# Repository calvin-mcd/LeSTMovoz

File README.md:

# LeSTMovoz
 
The LeSTMovoz is drop-in DIY replacement pcb for the [Lesovoz](https://trashman.wiki/community/pcbs/lesovoz) pcb by squash for [minivan](https://trashman.wiki/) style cases.
The replacement pcb adds a second 2u bottom row option by omitting one tray mount hole. [Existing plates](https://www.minivanplate.xyz/) should work but said 2u option is not accounted for in original plates.  

It uses mostly THT components to be added by hand, but production files exist to handle the few SMD components (STM32 mcu, logic shifter for rgb, usb port) with factory assembly.

Vial Firmware was created by JLW and can be found here: https://github.com/josh-l-wang/vial-qmk/tree/main-vial/keyboards/jlw/lestmovoz

## Layout

[Link](http://www.keyboard-layout-editor.com/#/gists/4bbcc5860d075f44de381a1146810c87)

## Todo

- [x] order & test pcb Rev 2
- [x] create firmware

## Disclaimer

This PCB has been fully tested and is confirmed to work. However, no-one involved in this project is responsible for any usage issues that may arise. Order at your own risk. Feel free to edit, modify and otherwise utilise these files.

## License

This project is released under the GPL v3 License. Please refer to the LICENCE file.

## Credits

Big thanks to JLW for supporting and making this project possible and to Kenny for getting it out there to people.

And as always big thanks to the 40s community!

Any questions, contact calvin0563 on Discord.

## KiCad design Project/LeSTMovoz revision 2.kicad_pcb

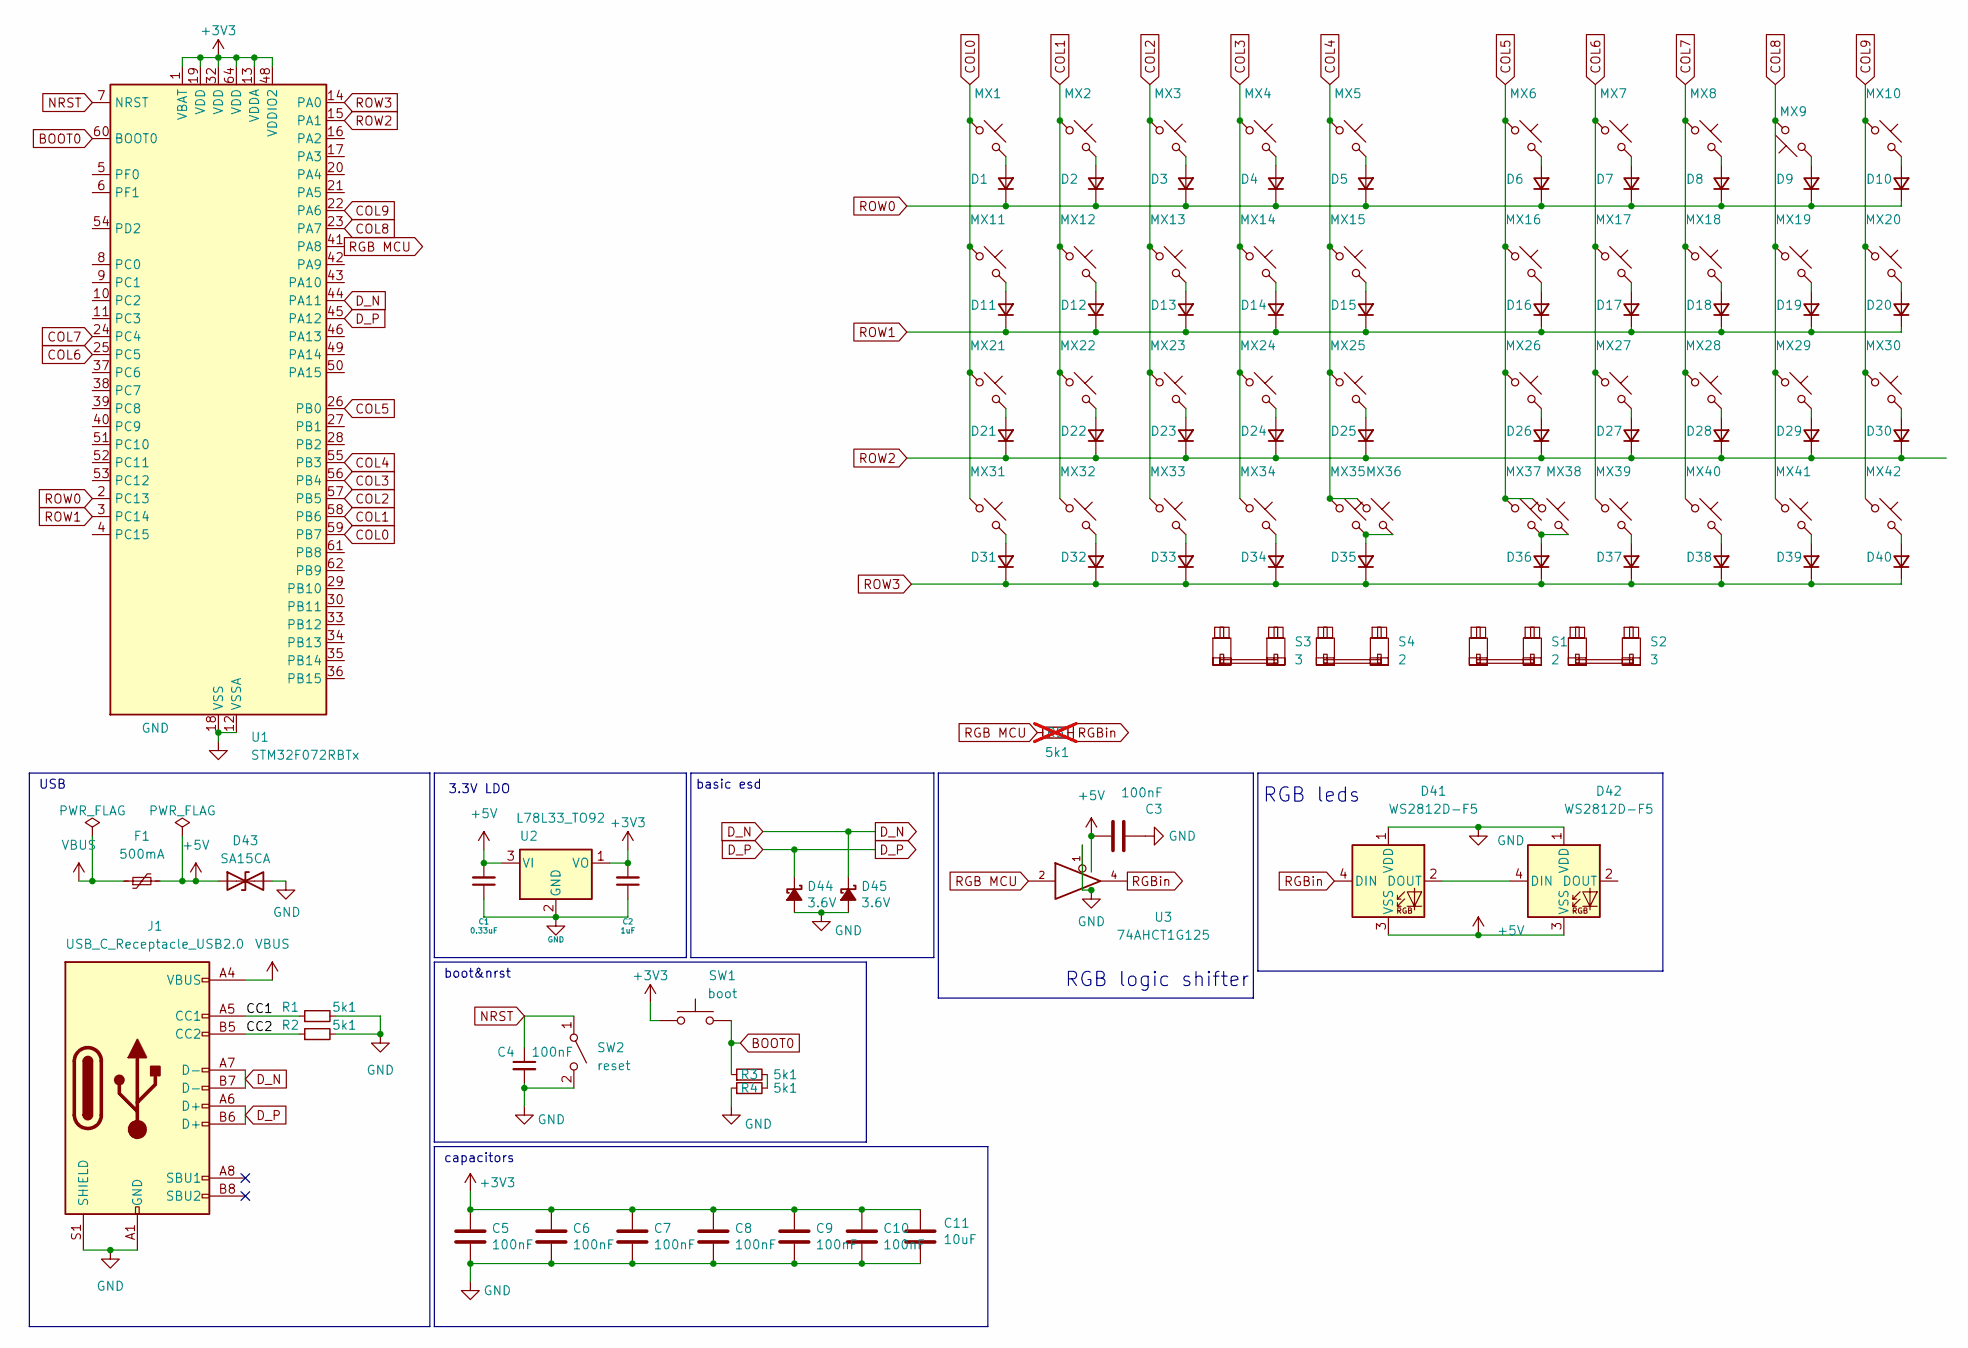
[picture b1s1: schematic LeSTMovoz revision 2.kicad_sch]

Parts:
C1: 0.33uF; C_Disc_D4.3mm_W1.9mm_P5.00mm
C2: 1uF; C_Disc_D4.3mm_W1.9mm_P5.00mm
C3, C4, C5, C6, C7, C8, C9, C10: 100nF; C_Disc_D4.3mm_W1.9mm_P5.00mm
C11: 10uF; C_Disc_D4.3mm_W1.9mm_P5.00mm
D1, D2, D3, D4, D5, D6, D7, D8, D9, D10, D11, D12, D13, D14, D15, D16, D17, D18, D19, D20, D21, D22, D23, D24, D25, D26, D27, D28, D29, D30, D31, D32, D33, D34, D35, D36, D37, D38, D39, D40: D_Small; D3_TH_SMD_v3
D41, D42: WS2812D-F5; NeoPixel_bulb_5mm_Adafruit_1938
D43: SA15CA; D_DO-15_P10.16mm_Horizontal
D44, D45: 3.6V; D_DO-35_SOD27_P7.62mm_Horizontal
F1: 500mA; Fuse_Bourns_MF-RHT100
J1: USB_C_Receptacle_USB2.0; USB_C_Receptacle_HRO_TYPE-C-31-M-12; LCSC C165948
MX1, MX2, MX3, MX4, MX5, MX6, MX7, MX8, MX9, MX10, MX11, MX12, MX13, MX14, MX15, MX16, MX17, MX18, MX19, MX20, MX21, MX22, MX23, MX24, MX25, MX26, MX27, MX28, MX29, MX30, MX31, MX32, MX33, MX34, MX35, MX36, MX37, MX38, MX39, MX40, MX41, MX42: MX_SW_solder; MX-Alps-Hybrid-1U
R1, R2, R3, R4: 5k1; R_Axial_DIN0204_L3.6mm_D1.6mm_P7.62mm_Horizontal
R5: 5k1; R_Axial_DIN0204_L3.6mm_D1.6mm_P7.62mm_Horizontal; not fitted
S1, S4: 2; STAB_MX_P_2u
S2, S3: 3; STAB_MX_P_3u
SW1: boot; SW_PUSH_6mm_H4.3mm; LCSC C115351
SW2: reset; SW_PUSH_6mm_H4.3mm; LCSC C115351
U1: STM32F072RBTx; LQFP-64_10x10mm_P0.5mm
U2: L78L33_TO92; TO-92_Inline
U3: 74AHCT1G125; TSOT-23-5_HandSoldering; LCSC C12494

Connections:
+3V3: C2.2, C5.1, C6.1, C7.1, C8.1, C9.1, C10.1, C11.1, SW1.1, U1.1 (VBAT), U1.13 (VDDA), U1.19 (VDD), U1.32 (VDD), U1.48 (VDDIO2), U1.64 (VDD), U2.1 (VO)
+5V: C1.2, C3.1, D41.3 (VSS), D42.3 (VSS), D43.1 (A1), F1.2, U2.3 (VI), U3.5 (+5V)
/CC1: J1.A5 (CC1), R1.1
/CC2: J1.B5 (CC2), R2.1
BOOT0: R3.1, SW1.2, U1.60 (BOOT0)
COL0: MX1.1, MX11.1, MX21.1, MX31.1, U1.59 (PB7)
COL1: MX2.1, MX12.1, MX22.1, MX32.1, U1.58 (PB6)
COL2: MX3.1, MX13.1, MX23.1, MX33.1, U1.57 (PB5)
COL3: MX4.1, MX14.1, MX24.1, MX34.1, U1.56 (PB4)
COL4: MX5.1, MX15.1, MX25.1, MX35.1, MX36.1, U1.55 (PB3)
COL5: MX6.1, MX16.1, MX26.1, MX37.1, MX38.1, U1.26 (PB0)
COL6: MX7.1, MX17.1, MX27.1, MX39.1, U1.25 (PC5)
COL7: MX8.1, MX18.1, MX28.1, MX40.1, U1.24 (PC4)
COL8: MX9.2, MX19.1, MX29.1, MX41.1, U1.23 (PA7)
COL9: MX10.1, MX20.1, MX30.1, MX42.1, U1.22 (PA6)
D_N: D45.1 (K), J1.A7 (D-), J1.B7 (D-), U1.44 (PA11)
D_P: D44.1 (K), J1.A6 (D+), J1.B6 (D+), U1.45 (PA12)
GND: C1.1, C2.1, C3.2, C4.2, C5.2, C6.2, C7.2, C8.2, C9.2, C10.2, C11.2, D41.1 (VDD), D42.1 (VDD), D43.2 (A2), D44.2 (A), D45.2 (A), J1.A1 (GND), J1.A12 (GND), J1.B1 (GND), J1.B12 (GND), J1.S1 (SHIELD), R1.2, R2.2, R4.1, SW2.2 (B), U1.12 (VSSA), U1.18 (VSS), U1.31 (VSS), U1.47 (VSS), U1.63 (VSS), U2.2 (GND), U3.1, U3.3 (GND)
NRST: C4.1, SW2.1 (A), U1.7 (NRST)
unnamed: D1.2 (A), MX1.2
unnamed: D2.2 (A), MX2.2
unnamed: D3.2 (A), MX3.2
unnamed: D4.2 (A), MX4.2
unnamed: D5.2 (A), MX5.2
unnamed: D6.2 (A), MX6.2
unnamed: D7.2 (A), MX7.2
unnamed: D8.2 (A), MX8.2
unnamed: D9.2 (A), MX9.1
unnamed: D10.2 (A), MX10.2
unnamed: D11.2 (A), MX11.2
unnamed: D12.2 (A), MX12.2
unnamed: D13.2 (A), MX13.2
unnamed: D14.2 (A), MX14.2
unnamed: D15.2 (A), MX15.2
unnamed: D16.2 (A), MX16.2
unnamed: D17.2 (A), MX17.2
unnamed: D18.2 (A), MX18.2
unnamed: D19.2 (A), MX19.2
unnamed: D20.2 (A), MX20.2
unnamed: D21.2 (A), MX21.2
unnamed: D22.2 (A), MX22.2
unnamed: D23.2 (A), MX23.2
unnamed: D24.2 (A), MX24.2
unnamed: D25.2 (A), MX25.2
unnamed: D26.2 (A), MX26.2
unnamed: D27.2 (A), MX27.2
unnamed: D28.2 (A), MX28.2
unnamed: D29.2 (A), MX29.2
unnamed: D30.2 (A), MX30.2
unnamed: D31.2 (A), MX31.2
unnamed: D32.2 (A), MX32.2
unnamed: D33.2 (A), MX33.2
unnamed: D34.2 (A), MX34.2
unnamed: D35.2 (A), MX35.2, MX36.2
unnamed: D36.2 (A), MX37.2, MX38.2
unnamed: D37.2 (A), MX39.2
unnamed: D38.2 (A), MX40.2
unnamed: D39.2 (A), MX41.2
unnamed: D40.2 (A), MX42.2
unnamed: D41.2 (DOUT), D42.4 (DIN)
unnamed: R3.2, R4.2
RGB MCU: R5.1, U1.41 (PA8), U3.2
RGBin: D41.4 (DIN), R5.2, U3.4
ROW0: D1.1 (K), D2.1 (K), D3.1 (K), D4.1 (K), D5.1 (K), D6.1 (K), D7.1 (K), D8.1 (K), D9.1 (K), D10.1 (K), U1.2 (PC13)
ROW1: D11.1 (K), D12.1 (K), D13.1 (K), D14.1 (K), D15.1 (K), D16.1 (K), D17.1 (K), D18.1 (K), D19.1 (K), D20.1 (K), U1.3 (PC14)
ROW2: D21.1 (K), D22.1 (K), D23.1 (K), D24.1 (K), D25.1 (K), D26.1 (K), D27.1 (K), D28.1 (K), D29.1 (K), D30.1 (K), U1.15 (PA1)
ROW3: D31.1 (K), D32.1 (K), D33.1 (K), D34.1 (K), D35.1 (K), D36.1 (K), D37.1 (K), D38.1 (K), D39.1 (K), D40.1 (K), U1.14 (PA0)
VBUS: F1.1, J1.A4 (VBUS), J1.A9 (VBUS), J1.B4 (VBUS), J1.B9 (VBUS)

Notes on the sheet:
RGB leds
RGB logic shifter
capacitors
boot&nrst
3.3V LDO
USB
basic esd

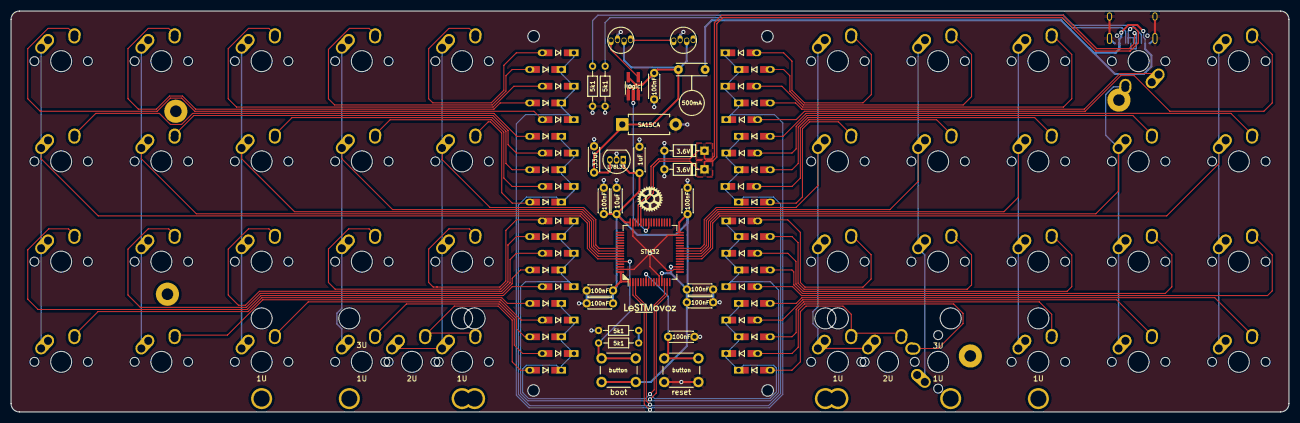
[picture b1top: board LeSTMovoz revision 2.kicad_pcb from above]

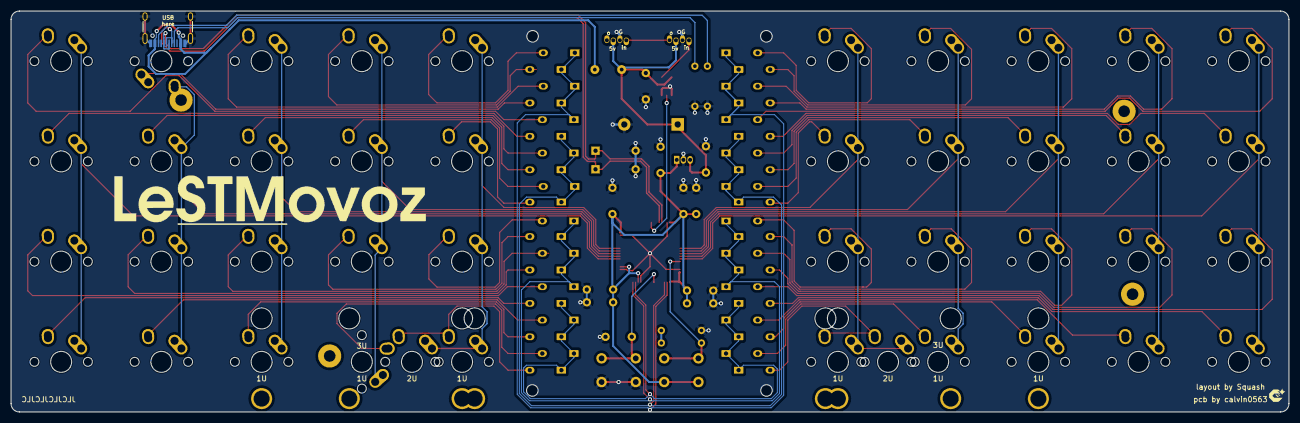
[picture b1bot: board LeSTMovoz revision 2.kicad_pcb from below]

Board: 2 copper layers, 242.9 x 76.2 mm, 114 parts (3 on the bottom side), 68 nets.

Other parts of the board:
H6: MountingHole_Pad; MountingHole_2.2mm_M2_Pad

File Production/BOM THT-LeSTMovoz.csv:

Comment,Designator,Amount,Footprint,LCSC
SW_SPST,"RST1,SW1",2,SW_SPST_SKQG_WithStem,C115351
74AHCT1G125,U3,1,TSOT-23-5_HandSoldering,C12494
STM32F072RBTx,U1,1,LQFP-64_10x10mm_P0.5mm,C46046
500mA,F1,1,Fuse_Bourns_MF-RHT100,C1562377 
100nF,"C3, C4, C5, C6, C7, C8, C9, C12 ",8,C_Disc_D4.3mm_W1.9mm_P5.00mm,C527620
5k1,"R4, R5",2,R_Axial_DIN0204_L3.6mm_D1.6mm_P7.62mm_Horizontal,C1370648
75R,"R2, R3",2,R_Axial_DIN0204_L3.6mm_D1.6mm_P7.62mm_Horizontal,C3495384 
0.33uF,C1,1,C_Disc_D4.3mm_W1.9mm_P5.00mm,C454409 
SA15CA,D41,1,D_DO-15_P10.16mm_Horizontal,C7466191
1.5k,R1,1,R_Axial_DIN0204_L3.6mm_D1.6mm_P7.62mm_Horizontal,C1369547 
3.6V,"D42, D43",2,D_DO-35_SOD27_P7.62mm_Horizontal,C895320 
L78L33_TO92,U2,1,TO-92_Inline,C2927581 
10uF,C10,1,C_Disc_D4.3mm_W1.9mm_P5.00mm,C454408
10k,R6,1,R_Axial_DIN0204_L3.6mm_D1.6mm_P7.62mm_Horizontal,C1420778
1uF,C2,1,C_Disc_D4.3mm_W1.9mm_P5.00mm,C454378
USB_C_Receptacle_USB2.0,J1,1,USB_C_Receptacle_GCT_USB4085,C2840393 
WS2812B,"D44, D45",2,WS2812B,C190565 
D3_TH_SMD_v2,D1  D40,40,,C85057
,,,,C402212

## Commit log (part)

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2024-02-11 initialise, add pictures, update readme
2024-02-11 clean up folder
2024-02-23 fresh gerbers
2024-02-23 backup
2024-03-09 changed rgb component, 10k for 2*5k1 resistors, finished THT BOM
2024-03-30 backups of revision work
2024-04-13 revision wip
2024-04-29 gerbers for revision
2025-03-01 revison work
2025-03-23 production files
